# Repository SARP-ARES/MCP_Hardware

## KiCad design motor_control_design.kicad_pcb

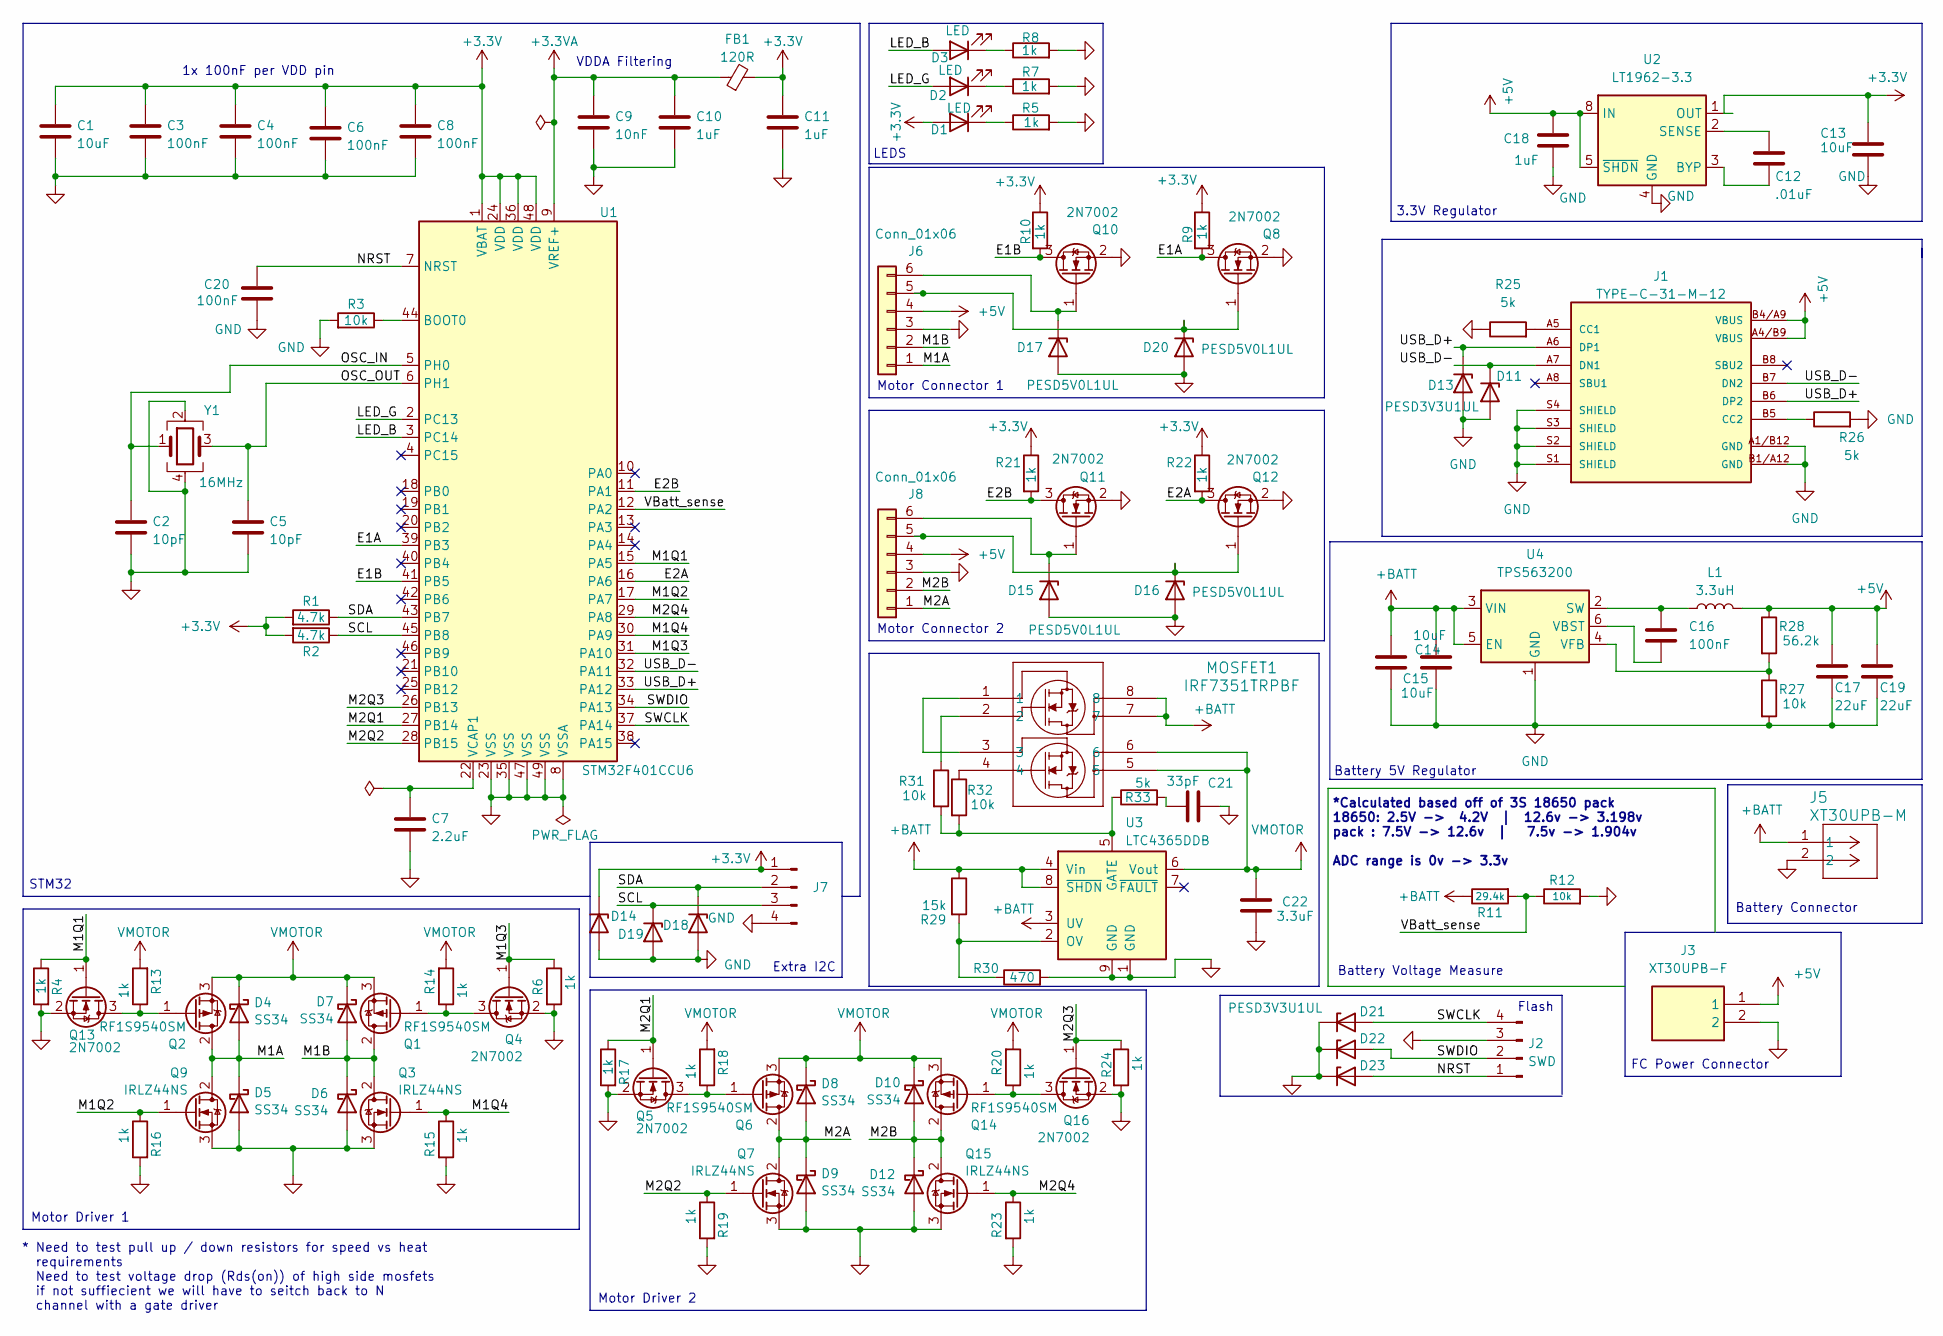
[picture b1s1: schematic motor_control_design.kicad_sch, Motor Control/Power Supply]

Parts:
C1: 10uF; C_0402_1005Metric; LCSC Part C19702
C2, C5: 10pF; C_0402_1005Metric; LCSC Part C32949
C3, C4, C6, C8: 100nF; C_0402_1005Metric; LCSC Part C307331
C7: 2.2uF; C_0402_1005Metric; LCSC Part C12530
C9: 10nF; C_0402_1005Metric; LCSC Part C15195
C10, C11: 1uF; C_0402_1005Metric; LCSC Part C52923
C12: .01uF; C_0402_1005Metric; LCSC Part C15195
C13, C14, C15: 10uF; C_0402_1005Metric; LCSC Part C315248
C16, C20: 100nF; C_0402_1005Metric; LCSC Part C1525
C17, C19: 22uF; C_0402_1005Metric; LCSC Part C3845593
C18: 1uF; C_0402_1005Metric; LCSC Part C14445
C21: 33pF; C_0402_1005Metric; LCSC Part C70465
C22: 3.3uF; C_0603_1608Metric; LCSC Part C51412
D1: LED; LED_0603_1608Metric; LCSC Part C9900011154
D2: LED; LED_0603_1608Metric; LCSC Part C779453
D3: LED; LED_0603_1608Metric; LCSC Part C131286
D4, D5, D6, D7, D8, D9, D10, D12: SS34; D_SMA; LCSC Part C3032484
D11, D13, D14, D18, D19, D21, D22, D23: PESD3V3U1UL; D_0402_1005Metric; LCSC Part C19829543
D15, D16, D17, D20: PESD5V0L1UL; D_SOD-882; LCSC Part C3001948
FB1: 120R; L_0603_1608Metric; LCSC Part C85831
J1: TYPE-C-31-M-12; USB_C_Receptacle_HRO_TYPE-C-31-M-12--MODIFIED; PARTREV 2020.12.08; LCSC Part C165948
J2: SWD; PinHeader_1x04_P2.54mm_Vertical; LCSC Part C160390
J3: XT30UPB-F; XT30UPBF; Manufacturer_Part_Number XT30UPB-F; LCSC Part C108769
J5: XT30UPB-M; CONN_XT30UPB-M_AMA; LCSC Part C428721
J6, J8: Conn_01x06; CONN_S6B-XH-SM4-TB_JST; LCSC Part C191914
J7: Conn_01x04_Pin; JST_SH_BM04B-SRSS-TB_1x04-1MP_P1.00mm_Vertical; LCSC Part C160390
L1: 3.3uH; L_0402_1005Metric; LCSC Part C7153195
MOSFET1: IRF7351TRPBF; PG-DSO-8-902_INF; LCSC Part C68403
Q1, Q2, Q6, Q14: RF1S9540SM; TO-263-2; LCSC Part C33903
Q3, Q7, Q9, Q15: IRLZ44NS; TO-263-2; LCSC Part C538199
Q4, Q5, Q8, Q10, Q11, Q12, Q13, Q16: 2N7002; SOT-23; LCSC Part C466660
R1, R2: 4.7k; R_0402_1005Metric; LCSC Part C174364
R3: 10k; R_0402_1005Metric; LCSC Part C174364
R4, R5, R6, R7, R8, R9, R10, R13, R14, R15, R16, R17, R18, R19, R20, R21, R22, R23, R24: 1k; R_0402_1005Metric; LCSC Part C102758
R11: 29.4k; R_0402_1005Metric; LCSC Part C162880
R12: 10k; R_0402_1005Metric; LCSC Part C176114
R25, R26, R33: 5k; R_0402_1005Metric; LCSC Part C166638
R27, R31, R32: 10k; R_0402_1005Metric; LCSC Part C25531
R28: 56.2k; R_0402_1005Metric; LCSC Part C54968
R29: 15k; R_0402_1005Metric; LCSC Part C25539
R30: 470; R_0603_1608Metric; LCSC Part C25117
U1: STM32F401CCU6; QFN-48-1EP_7x7mm_P0.5mm_EP5.6x5.6mm; LCSC Part C79861
U2: LT1962-3.3; MSOP-8_3x3mm_P0.65mm; LCSC Part C107774
U3: LTC4365DDB; DFN-8-1EP_2x3mm_P0.5mm_EP0.61x2.2mm; LCSC Part C688318
U4: TPS563200; SOT-23-6; LCSC Part C97253
Y1: 16MHz; Crystal_SMD_3225-4Pin_3.2x2.5mm; LCSC Part C13738

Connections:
+3.3V: C1.1, C3.1, C4.1, C6.1, C8.1, C11.1, C13.1, D1.2 (A), D14.1 (K), FB1.2, J7.1, R1.2, R2.2, R9.1, R10.1, R21.1, R22.1, U1.1 (VBAT), U1.24 (VDD), U1.36 (VDD), U1.48 (VDD), U2.1 (OUT)
+3.3VA: C9.1, C10.1, FB1.1, U1.9 (VREF+)
+5V: C17.1, C18.1, C19.1, J1.A4/B9 (VBUS), J1.B4/A9 (VBUS), J3.1, J6.4, J8.4, L1.2, R28.1, U2.5 (~SHDN), U2.8 (IN)
+BATT: C14.2, C15.1, J5.1, MOSFET1.7, MOSFET1.8, R11.1, R29.1, U3.3 (UV), U3.4 (Vin), U3.8 (~SHDN), U4.3 (VIN), U4.5 (EN)
/E1A: Q8.3 (D), R9.2, U1.39 (PB3)
/E1B: Q10.3 (D), R10.2, U1.41 (PB5)
/E2A: Q12.3 (D), R22.2, U1.16 (PA6)
/E2B: Q11.3 (D), R21.2, U1.11 (PA1)
/LED_B: D3.2 (A), U1.3 (PC14)
/LED_G: D2.2 (A), U1.2 (PC13)
/M1A: D4.2 (A), D5.1 (K), J6.1, Q2.2 (D), Q9.2 (D)
/M1B: D6.1 (K), D7.2 (A), J6.2, Q1.2 (D), Q3.2 (D)
/M1Q1: Q13.1 (G), R4.1, U1.15 (PA5)
/M1Q2: Q9.1 (G), R16.1, U1.17 (PA7)
/M1Q3: Q4.1 (G), R6.1, U1.31 (PA10)
/M1Q4: Q3.1 (G), R15.1, U1.30 (PA9)
/M2A: D8.2 (A), D9.1 (K), J8.1, Q6.2 (D), Q7.2 (D)
/M2B: D10.2 (A), D12.1 (K), J8.2, Q14.2 (D), Q15.2 (D)
/M2Q1: Q5.1 (G), R17.1, U1.27 (PB14)
/M2Q2: Q7.1 (G), R19.1, U1.28 (PB15)
/M2Q3: Q16.1 (G), R24.1, U1.26 (PB13)
/M2Q4: Q15.1 (G), R23.1, U1.29 (PA8)
/NRST: C20.1, D23.2 (A), J2.1, U1.7 (NRST)
/OSC_IN: C2.1, U1.5 (PH0), Y1.1
/OSC_OUT: C5.1, U1.6 (PH1), Y1.3
/SCL: D19.1 (K), J7.3, R2.1, U1.45 (PB8)
/SDA: D18.1 (K), J7.2, R1.1, U1.43 (PB7)
/SWCLK: D21.2 (A), J2.4, U1.37 (PA14)
/SWDIO: D22.2 (A), J2.2, U1.34 (PA13)
/USB_D+: D13.1 (K), J1.A6 (DP1), J1.B6 (DP2), U1.33 (PA12)
/USB_D-: D11.1 (K), J1.A7 (DN1), J1.B7 (DN2), U1.32 (PA11)
/VBatt_sense: R11.2, R12.1, U1.12 (PA2)
GND: C1.2, C2.2, C3.2, C4.2, C5.2, C6.2, C7.2, C8.2, C9.2, C10.2, C11.2, C13.2, C14.1, C15.2, C17.2, C18.2, C19.2, C20.2, C21.2, C22.2, D5.2 (A), D6.2 (A), D9.2 (A), D11.2 (A), D12.2 (A), D13.2 (A), D14.2 (A), D15.2 (A), D16.2 (A), D17.2 (A), D18.2 (A), D19.2 (A), D20.2 (A), D21.1 (K), D22.1 (K), D23.1 (K), J1.A1/B12 (GND), J1.B1/A12 (GND), J1.S1 (SHIELD), J1.S2 (SHIELD), J1.S3 (SHIELD), J1.S4 (SHIELD), J2.3, J3.2, J5.2, J6.3, J7.4, J8.3, Q3.3 (S), Q4.2 (S), Q5.2 (S), Q7.3 (S), Q8.2 (S), Q9.3 (S), Q10.2 (S), Q11.2 (S), Q12.2 (S), Q13.2 (S), Q15.3 (S), Q16.2 (S), R3.2, R4.2, R5.2, R6.2, R7.2, R8.2, R12.2, R15.2, R16.2, R17.2, R19.2, R23.2, R24.2, R25.1, R26.2, R27.2, R30.2, U1.8 (VSSA), U1.23 (VSS), U1.35 (VSS), U1.47 (VSS), U1.49 (VSS), U2.4 (GND), U3.1 (GND), U3.9 (GND), U4.1 (GND), Y1.2, Y1.4
unnamed: C21.1, R33.2
unnamed: D1.1 (K), R5.1
unnamed: D2.1 (K), R7.1
unnamed: D3.1 (K), R8.1
unnamed: D15.1 (K), J8.6, Q11.1 (G)
unnamed: D16.1 (K), J8.5, Q12.1 (G)
unnamed: D17.1 (K), J6.6, Q10.1 (G)
unnamed: D20.1 (K), J6.5, Q8.1 (G)
unnamed: J1.A5 (CC1), R25.2
unnamed: J1.B5 (CC2), R26.1
unnamed: MOSFET1.1, MOSFET1.3
unnamed: MOSFET1.2, R31.1
unnamed: MOSFET1.4, R32.1
unnamed: Q1.1 (G), Q4.3 (D), R14.1
unnamed: Q5.3 (D), Q6.1 (G), R18.1
unnamed: Q2.1 (G), Q13.3 (D), R13.1
unnamed: Q14.1 (G), Q16.3 (D), R20.1
unnamed: R3.1, U1.44 (BOOT0)
unnamed: C7.1, U1.22 (VCAP1)
unnamed: C12.2, U2.3 (BYP)
unnamed: C12.1, U2.2 (SENSE)
unnamed: R31.2, R32.2, R33.1, U3.5 (GATE)
unnamed: R29.2, R30.1, U3.2 (OV)
unnamed: C16.1, L1.1, U4.2 (SW)
unnamed: C16.2, U4.6 (VBST)
unnamed: R27.1, R28.2, U4.4 (VFB)
VMOTOR: C22.1, D4.1 (K), D7.1 (K), D8.1 (K), D10.1 (K), MOSFET1.5, MOSFET1.6, Q1.3 (S), Q2.3 (S), Q6.3 (S), Q14.3 (S), R13.2, R14.2, R18.2, R20.2, U3.6 (Vout)

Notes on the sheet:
Battery 5V Regulator
Motor Driver 1
Extra I2C
Motor Connector 1
* Need to test pull up / down resistors for speed vs heat requirements Need to test voltage drop (Rds(on)) of high side mosfets if not suffiecient we will have to seitch back to N channel with a gate driver
3.3V Regulator
*Calculated based off of 3S 18650 pack 18650: 2.5V -> 4.2V | 12.6v -> 3.198v pack : 7.5V -> 12.6v | 7.5v -> 1.904v ADC range is 0v -> 3.3v
Motor Connector 2
Motor Driver 2
FC Power Connector
Battery Connector
Battery Voltage Measure
VDDA Filtering
Flash
1x 100nF per VDD pin
LEDS
STM32

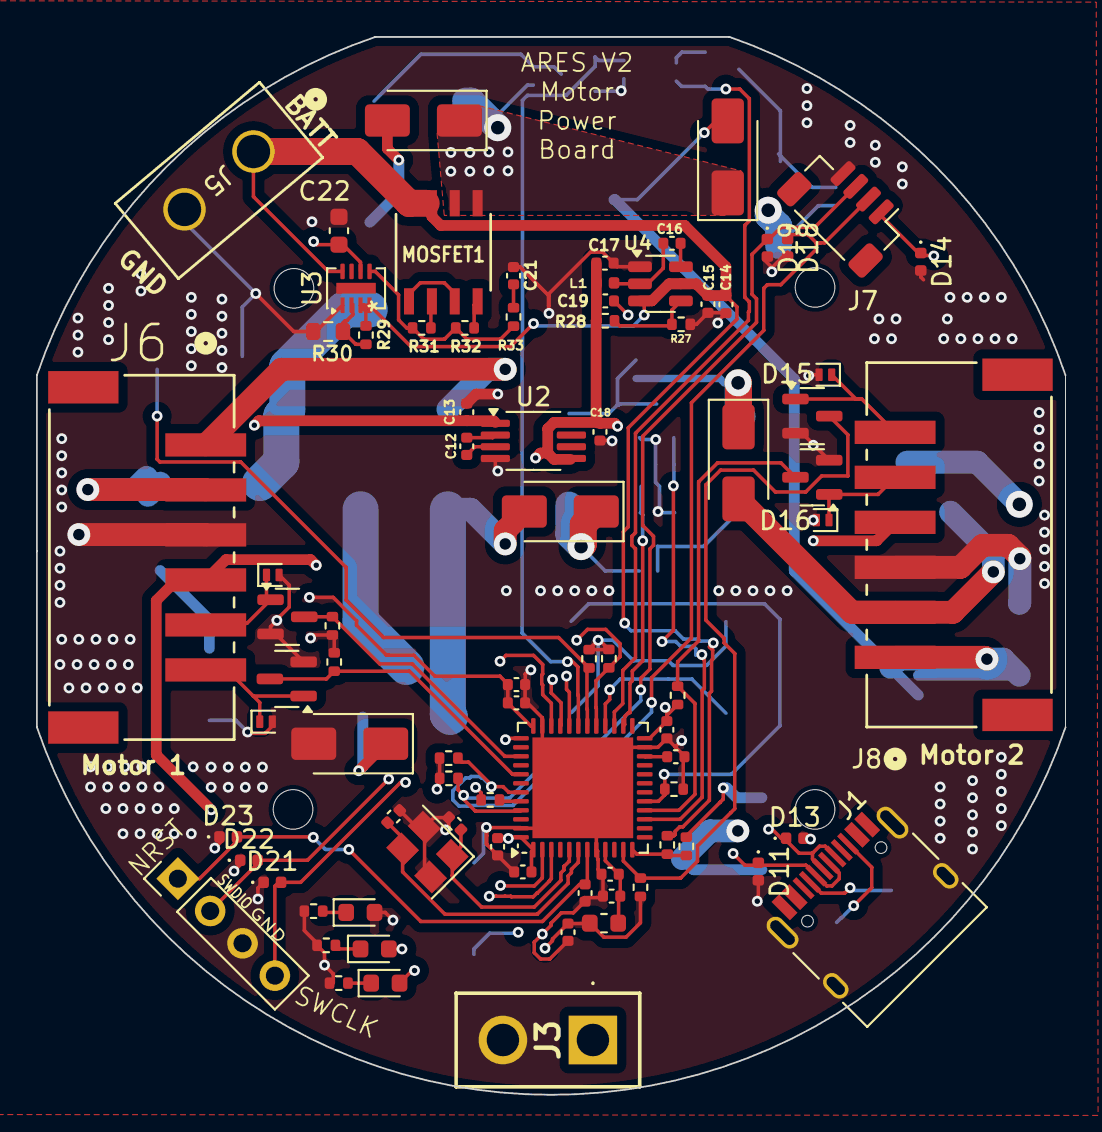
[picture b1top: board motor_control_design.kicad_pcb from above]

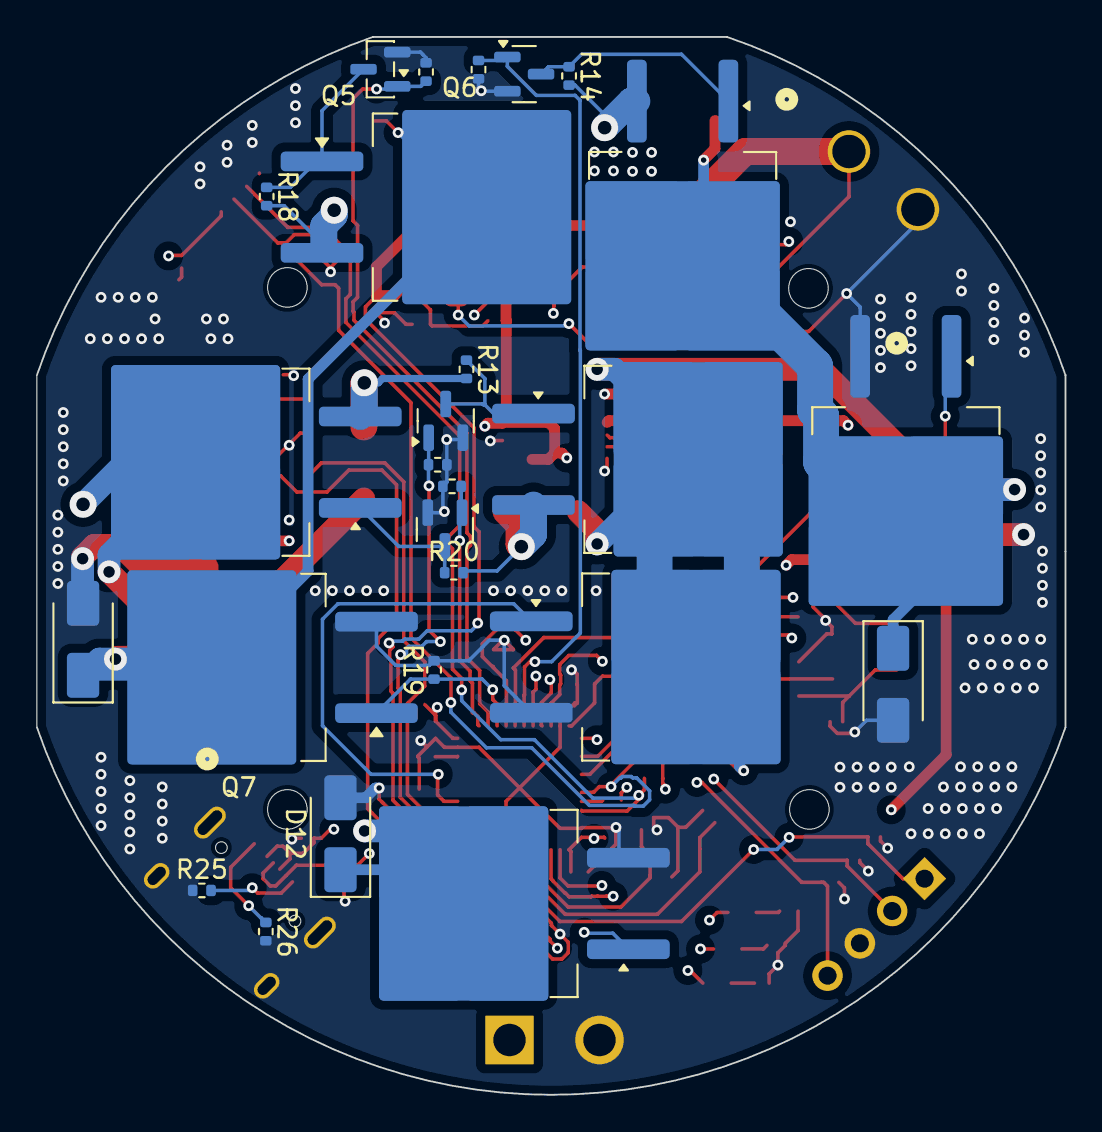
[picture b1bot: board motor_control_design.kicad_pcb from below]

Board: 4 copper layers, 57.1 x 58.8 mm, 109 parts (26 on the bottom side), 60 nets.

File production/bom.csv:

Designator,Footprint,Quantity,Value,LCSC Part #
"_4, _3, _2, ",,4,,
C1,0402,1,10uF,C19702
"C10, C11",0402,2,1uF,C52923
C12,0402,1,.01uF,C15195
"C13, C14, C15",0402,3,10uF,C315248
"C16, C20",0402,2,100nF,C1525
"C17, C19",0402,2,22uF,C3845593
C18,0402,1,1uF,C14445
"C2, C5",0402,2,10pF,C32949
C21,0402,1,33pF,C70465
C22,0603,1,3.3uF,
"C3, C4, C6, C8",0402,4,100nF,C307331
C7,0402,1,2.2uF,C12530
C9,0402,1,10nF,C15195
D1,0603,1,LED,C9900011154
"D10, D12, D4, D5, D6, D7, D8, D9",D_SMA,8,SS34,C3032484
"D11, D13, D14, D18, D19, D21, D22, D23",D_SOD-882,8,PESD3V3U1UL,
"D15, D16, D17, D20",D_SOD-882,4,PESD5V0L1UL,
D2,0603,1,LED,C779453
D3,0603,1,LED,C131286
FB1,0603,1,120R,C85831
J1,USB_C_Receptacle_HRO_TYPE-C-31-M-12--MODIFIED,1,TYPE-C-31-M-12,C165948
J2,PinHeader_1x04_P2.54mm_Vertical,1,SWD,
J3,XT30UPBF,1,XT30UPB-F,
J5,CONN_XT30UPB-M_AMA,1,XT30UPB-M,
"J6, J8",CONN_S6B-XH-SM4-TB_JST,2,Conn_01x06,
J7,JST_SH_BM04B-SRSS-TB_1x04-1MP_P1.00mm_Vertical,1,Conn_01x04_Pin,C160390
L1,0402,1,3.3uH,
MOSFET1,PG-DSO-8-902_INF,1,IRF7351TRPBF,
"Q1, Q14, Q2, Q6",TO-263-2,4,RF1S9540SM, C33903
"Q10, Q11, Q12, Q13, Q16, Q4, Q5, Q8",SOT-23,8,2N7002,C466660
"Q15, Q3, Q7, Q9",TO-263-2,4,IRLZ44NS, C538199
"R1, R2",0402,2,4.7k,C174364
"R10, R13, R14, R15, R16, R17, R18, R19, R20, R21, R22, R23, R24, R4, R5, R6, R7, R8, R9",0402,19,1k,C102758
R11,0402,1,29.4k,C162880
R12,0402,1,10k,C176114
"R25, R26",0402,2,5.11k,
"R27, R31, R32",0402,3,10k,
R28,0402,1,56.2k,
R29,0402,1,15k,
R3,0402,1,10k,C174364
R30,0603,1,470,
R33,0402,1,5.1k,
U1,QFN-48-1EP_7x7mm_P0.5mm_EP5.6x5.6mm,1,STM32F401CCU6,C79861
U2,MSOP-8_3x3mm_P0.65mm,1,LT1962-3.3,
U3,DFN-8-1EP_2x3mm_P0.5mm_EP0.61x2.2mm,1,LTC4365DDB,
U4,SOT-23-6,1,TPS563200,
Y1,Crystal_SMD_3225-4Pin_3.2x2.5mm,1,16MHz,C13738

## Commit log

2025-03-06 copied MCP Files from old repo
2025-07-31 Moved M1Q2 and E2B
2025-08-03 intermediate
2025-08-07 E2A Wired
2025-08-07 M1Q2 connected potential problems
2025-08-21 8v power to encoder schematic
2025-08-22 USBC schematic started, M1Q1 moved to PA5
2025-09-10 Working on new 5v 3.3v power sys
2025-09-20 Systems boxed, footprints added
2025-09-22 Routing, still messy
2025-09-22 I think main routing done?
2025-09-24 Working through DRC
2025-09-24 fixed LEDS?
2025-10-01 added i2c, moved batt and ground pads back from edge
2025-10-02 working on DRC
2025-10-08 TPS563200 Buck
2025-10-08 Connector, doc label changes
2025-10-08 ADR1 layout changes
2025-10-09 moved left motor connector
2025-10-10 Cleaned up traces after shifting last night
    Cleaned up traces after shifting last night
2025-10-10 ADR2
    Put the 8th mosfet back, fixed all of ethans criteia
2025-11-01 cleaned up NRST BOOT0 schematic
2025-11-03 Added LTC4365
2025-11-03 Overvoltage system schematic drafted
2025-11-03 updated overvoltage resistor values
2025-11-04 connected shdn
2025-11-04 vbatt nets
2025-11-04 schematic tvs diode
2025-11-06 layout changes started, ov regulator wip
2025-11-07 layout completed with ov, tvs; only board edge and footprint drc err
2025-11-08 clean up
2025-11-11 nothing
2025-11-18 small changes
    fixed some ground plane connections, messed with the usbc footprint
2025-11-25 board edge tweaks
2025-11-25 drc: just acceptable board edge errs
2026-01-05 IRF layout 80%
2026-01-06 OV IC layout done
2026-01-06 added 5v label on silkscreen
2026-01-08 created branch
2026-01-08 original placement
2026-01-08 placement in progress
2026-01-08 placement 95% done
2026-01-09 routing progress
2026-01-09 0 drc errors
2026-01-12 xt30, cleaned up board
2026-01-16 silkscreen clean up
2026-01-17 added hella stitching vias and cleaned up some traces
2026-01-18 connector change, files prepared
2026-01-19 BUILD files
2026-01-28 changed resistor component
